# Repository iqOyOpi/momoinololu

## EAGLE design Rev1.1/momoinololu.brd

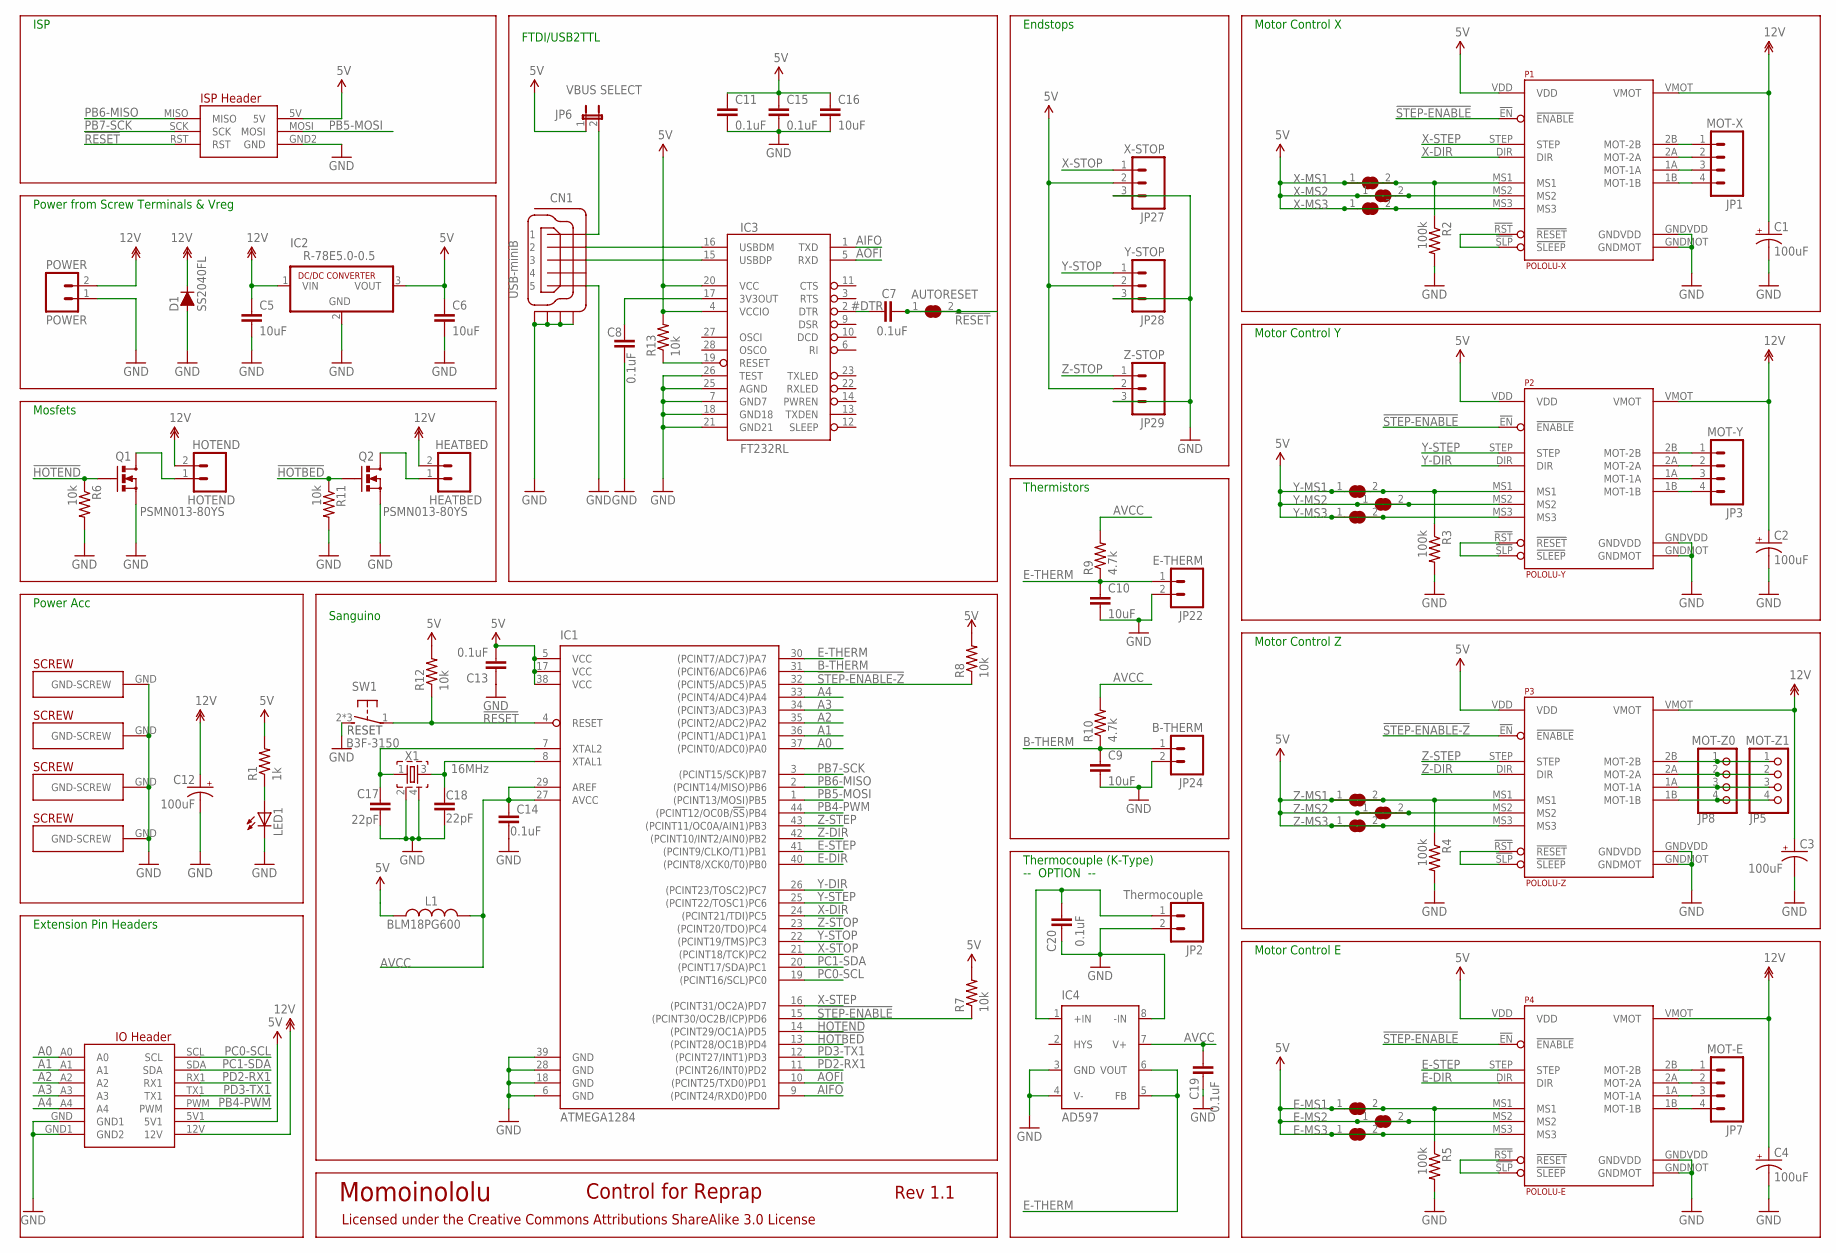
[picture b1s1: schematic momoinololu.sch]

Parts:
AUTORESET: SJ
C1, C2, C3, C4, C12: 100uF; UD-6,3X7,7_NICHICON
C5, C6, C9, C10, C16: 10uF; RCL_C1206K
C7, C8, C11, C13, C14, C15, C19, C20: 0.1uF; C0603
C17, C18: 22pF; C0603
CN1: USB-miniB; CON-HIROSE_UX60A-MB-5ST
D1: SS2040FL; SEMICON-SMD-IPC_SOD123
E-MS1, E-MS2, E-MS3: SJ
HEATBED: HEATBED; SCREWTERMINAL-5.08MM-2
HOTEND: HOTEND; SCREWTERMINAL-5.08MM-2
IC1: ATMEGA1284; TQFP44
IC2: R-78E5.0-0.5; SIP3
IC3: FT232RL; SSOP28DB
IC4: AD597; SO8
JP1: MOT-X; SPARKFUN_MOLEX-1X4
JP2: Thermocouple; SPARKFUN_1X02
JP3: MOT-Y; SPARKFUN_MOLEX-1X4
JP5: MOT-Z1; 1X04
JP6: VBUS SELECT; SPARKFUN_1X02
JP7: MOT-E; SPARKFUN_MOLEX-1X4
JP8: MOT-Z0; 1X04
JP22: E-THERM; SPARKFUN_1X02
JP24: B-THERM; SPARKFUN_1X02
JP27: X-STOP; SPARKFUN_MOLEX-1X3
JP28: Y-STOP; SPARKFUN_MOLEX-1X3
JP29: Z-STOP; SPARKFUN_MOLEX-1X3
L1: BLM18PG600; L0603
LED1: LEDSML0805; SML0805
P1: POLOLU-X; POLOLU-ALLEGRO_POLOLU-ALLEGRO-PTH
P2: POLOLU-Y; POLOLU-ALLEGRO_POLOLU-ALLEGRO-PTH
P3: POLOLU-Z; POLOLU-ALLEGRO_POLOLU-ALLEGRO-PTH
P4: POLOLU-E; POLOLU-ALLEGRO_POLOLU-ALLEGRO-PTH
POWER: POWER; SCREWTERMINAL-5.08MM-2
Q1, Q2: PSMN013-80YS; SOT669
R1: 1k; R0603
R2, R3, R4, R5: 100k; R0603
R6, R7, R8, R11, R12, R13: 10k; R0603
R9, R10: 4.7k; R0603
SW1: B3F-3150; B3F-31XX
U$17, U$20, U$25, U$31: PLATED-SCREW; PLATEDSCREW
U$24: SANGUINOLOLU_IO_HEADERSNOSCREW; SANGUINOLOLU_IO_HEADER_NOSCREW
X1: 16MHz; FA-238
X-MS1, X-MS2, X-MS3: SJ
Y-MS1, Y-MS2, Y-MS3: SJ
Z-MS1, Z-MS2, Z-MS3: SJ

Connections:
3V3: C8.1, IC3.17 (3V3OUT)
5V: C6.1, C11.1, C13.2, C15.1, C16.1, E-MS1.1, E-MS1.2, E-MS2.1, E-MS2.2, E-MS3.1, E-MS3.2, IC1.5 (VCC), IC1.17 (VCC), IC1.38 (VCC), IC2.3 (VOUT), IC3.4 (VCCIO), IC3.20 (VCC), JP6.1, JP27.2, JP28.2, JP29.2, L1.1, P1.MS1, P1.MS2, P1.MS3, P1.VDD, P2.MS1, P2.MS2, P2.MS3, P2.VDD, P3.MS1, P3.MS2, P3.MS3, P3.VDD, P4.MS1, P4.MS2, P4.MS3, P4.VDD, R1.2, R2.1, R3.1, R4.1, R5.1, R7.2, R8.2, R12.2, R13.2, U$24.5V, U$24.5V1, X-MS1.1, X-MS1.2, X-MS2.1, X-MS2.2, X-MS3.1, X-MS3.2, Y-MS1.1, Y-MS1.2, Y-MS2.1, Y-MS2.2, Y-MS3.1, Y-MS3.2, Z-MS1.1, Z-MS1.2, Z-MS2.1, Z-MS2.2, Z-MS3.1, Z-MS3.2
12V: C1.+, C2.+, C3.+, C4.+, C5.1, C12.+, D1.1 (C), HEATBED.2, HOTEND.2, IC2.1 (VIN), P1.VMOT, P2.VMOT, P3.VMOT, P4.VMOT, POWER.2, U$24.12V
!HOTBED: IC1.13 ((PCINT28/OC1B)PD4), Q2.4 (G), R11.1
!HOTEND: IC1.14 ((PCINT29/OC1A)PD5), Q1.4 (G), R6.1
!RESET: AUTORESET.1, AUTORESET.2, C7.1, IC1.4 (RESET), R12.1, SW1.1, U$24.RST
!STEP-ENABLE: IC1.15 ((PCINT30/OC2B/ICP)PD6), P1.!EN (!ENABLE), P2.!EN (!ENABLE), P4.!EN (!ENABLE), R7.1
!STEP-ENABLE-Z: IC1.32 ((PCINT5/ADC5)PA5), P3.!EN (!ENABLE), R8.1
#DTR: C7.2, IC3.2 (DTR)
+IN: C20.1, IC4.1 (+IN), JP2.1
A0: IC1.37 ((PCINT0/ADC0)PA0), U$24.A0
A1: IC1.36 ((PCINT1/ADC1)PA1), U$24.A1
A2: IC1.35 ((PCINT2/ADC2)PA2), U$24.A2
A3: IC1.34 ((PCINT3/ADC3)PA3), U$24.A3
A4: IC1.33 ((PCINT4/ADC4)PA4), U$24.A4
AIFO: IC1.9 ((PCINT24/RXD0)PD0), IC3.1 (TXD)
AOFI: IC1.10 ((PCINT25/TXD0)PD1), IC3.5 (RXD)
AVCC: C14.1, C19.1, IC1.27 (AVCC), IC1.29 (AREF), IC4.7 (V+), L1.2, R9.2, R10.2
B-THERM: C9.1, IC1.31 ((PCINT6/ADC6)PA6), JP24.1, R10.1
E-DIR: IC1.40 ((PCINT8/XCK0/T0)PB0), P4.DIR
E-MOT-1A: JP7.3, P4.1A (MOT-1A)
E-MOT-1B: JP7.4, P4.1B (MOT-1B)
E-MOT-2A: JP7.2, P4.2A (MOT-2A)
E-MOT-2B: JP7.1, P4.2B (MOT-2B)
E-RESETSLEEP: P4.!RST (!RESET), P4.!SLP (!SLEEP)
E-STEP: IC1.41 ((PCINT9/CLKO/T1)PB1), P4.STEP
E-THERM: C10.1, IC1.30 ((PCINT7/ADC7)PA7), IC4.5 (FB), IC4.6 (VOUT), JP22.1, R9.1
GND: C1.-, C2.-, C3.-, C4.-, C5.2, C6.2, C8.2, C9.2, C10.2, C11.2, C12.-, C13.1, C14.2, C15.2, C16.2, C17.2, C18.2, C19.2, C20.2, CN1.5, CN1.M1 (S1), CN1.M2 (S2), CN1.M3 (S3), CN1.M4 (S4), D1.2 (A), IC1.6 (GND), IC1.18 (GND), IC1.28 (GND), IC1.39 (GND), IC2.2 (GND), IC3.7 (GND7), IC3.18 (GND18), IC3.21 (GND21), IC3.25 (AGND), IC3.26 (TEST), IC4.3 (GND), IC4.4 (V-), IC4.8 (-IN), JP2.2, JP22.2, JP24.2, JP27.3, JP28.3, JP29.3, LED1.C, P1.GNDMOT, P1.GNDVDD, P2.GNDMOT, P2.GNDVDD, P3.GNDMOT, P3.GNDVDD, P4.GNDMOT, P4.GNDVDD, POWER.1, Q1.1 (S), Q1.2 (S), Q1.3 (S), Q2.1 (S), Q2.2 (S), Q2.3 (S), R2.2, R3.2, R4.2, R5.2, R6.2, R11.2, SW1.2 (S), SW1.3 (S), SW1.4 (S), U$17.GND, U$20.GND, U$24.GND (GND1), U$24.GND1 (GND2), U$24.GND2 (GND), U$25.GND, U$31.GND, X1.2, X1.4
HEATBED-GND: HEATBED.1, Q2.MB (D)
HOTEND-GND: HOTEND.1, Q1.MB (D)
LED1: LED1.A, R1.1
unnamed: C17.1, IC1.7 (XTAL2), X1.1
unnamed: IC3.19 (RESET), R13.1
unnamed: C18.1, IC1.8 (XTAL1), X1.3
unnamed: CN1.2, IC3.16 (USBDM)
unnamed: CN1.3, IC3.15 (USBDP)
PB4-PWM: IC1.44 ((PCINT12/OC0B/!SS!)PB4), U$24.PWM
PB5-MOSI: IC1.1 ((PCINT13/MOSI)PB5), U$24.MOSI
PB6-MISO: IC1.2 ((PCINT14/MISO)PB6), U$24.MISO
PB7-SCK: IC1.3 ((PCINT15/SCK)PB7), U$24.SCK
PC0-SCL: IC1.19 ((PCINT16/SCL)PC0), U$24.SCL
PC1-SDA: IC1.20 ((PCINT17/SDA)PC1), U$24.SDA
PD2-RX1: IC1.11 ((PCINT26/INT0)PD2), U$24.RX1
PD3-TX1: IC1.12 ((PCINT27/INT1)PD3), U$24.TX1
VBUS: CN1.1, JP6.2
X-DIR: IC1.24 ((PCINT21/TDI)PC5), P1.DIR
X-MOT-1A: JP1.3, P1.1A (MOT-1A)
X-MOT-1B: JP1.4, P1.1B (MOT-1B)
X-MOT-2A: JP1.2, P1.2A (MOT-2A)
X-MOT-2B: JP1.1, P1.2B (MOT-2B)
X-RESETSLEEP: P1.!RST (!RESET), P1.!SLP (!SLEEP)
X-STEP: IC1.16 ((PCINT31/OC2A)PD7), P1.STEP
X-STOP: IC1.21 ((PCINT18/TCK)PC2), JP27.1
Y-DIR: IC1.26 ((PCINT23/TOSC2)PC7), P2.DIR
Y-MOT-1A: JP3.3, P2.1A (MOT-1A)
Y-MOT-1B: JP3.4, P2.1B (MOT-1B)
Y-MOT-2A: JP3.2, P2.2A (MOT-2A)
Y-MOT-2B: JP3.1, P2.2B (MOT-2B)
Y-RESETSLEEP: P2.!RST (!RESET), P2.!SLP (!SLEEP)
Y-STEP: IC1.25 ((PCINT22/TOSC1)PC6), P2.STEP
Y-STOP: IC1.22 ((PCINT19/TMS)PC3), JP28.1
Z-DIR: IC1.42 ((PCINT10/INT2/AIN0)PB2), P3.DIR
Z-MOT-1A: JP5.3, JP8.3, P3.1A (MOT-1A)
Z-MOT-1B: JP5.4, JP8.4, P3.1B (MOT-1B)
Z-MOT-2A: JP5.2, JP8.2, P3.2A (MOT-2A)
Z-MOT-2B: JP5.1, JP8.1, P3.2B (MOT-2B)
Z-RESETSLEEP: P3.!RST (!RESET), P3.!SLP (!SLEEP)
Z-STEP: IC1.43 ((PCINT11/OC0A/AIN1)PB3), P3.STEP
Z-STOP: IC1.23 ((PCINT20/TDO)PC4), JP29.1

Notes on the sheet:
Motor Control X
Motor Control Y
Motor Control Z
Motor Control E
ISP
Thermistors
Endstops
Sanguino
FTDI/USB2TTL
Mosfets
Power Acc
Momoinololu
Rev 1.1
Control for Reprap
Licensed under the Creative Commons Attributions ShareAlike 3.0 License
Extension Pin Headers
Power from Screw Terminals & Vreg
Thermocouple (K-Type)
RESET
-- OPTION --

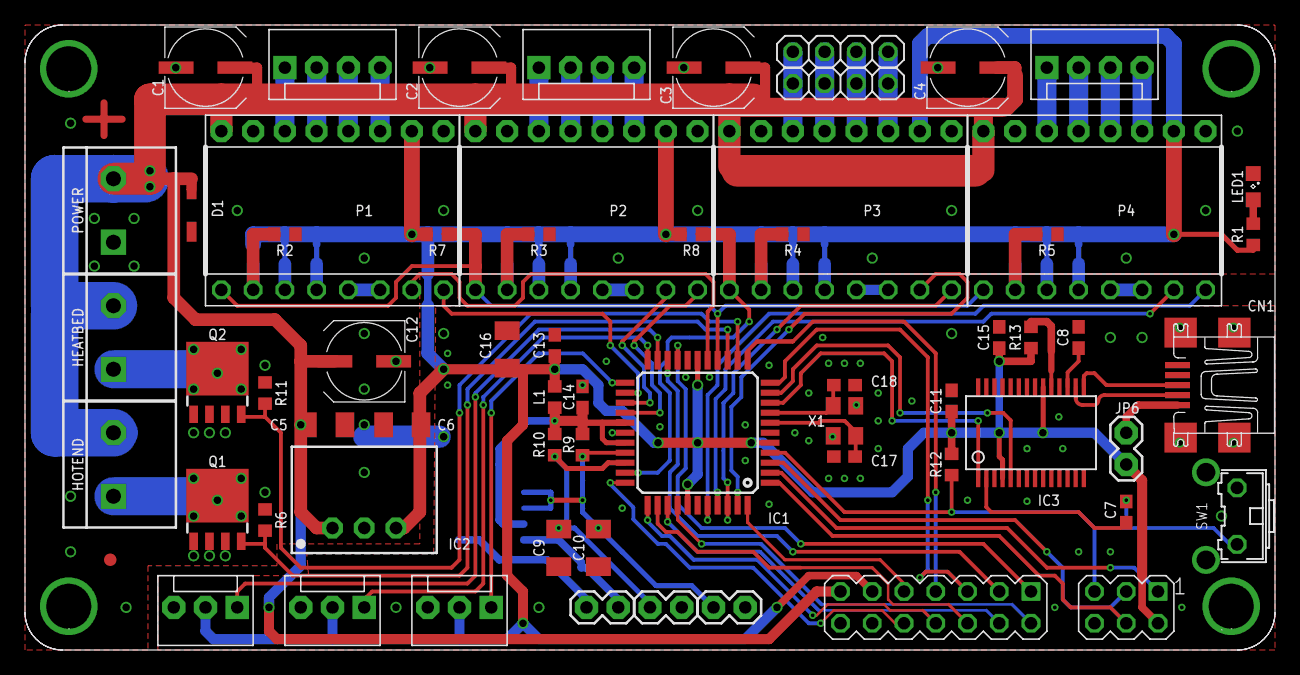
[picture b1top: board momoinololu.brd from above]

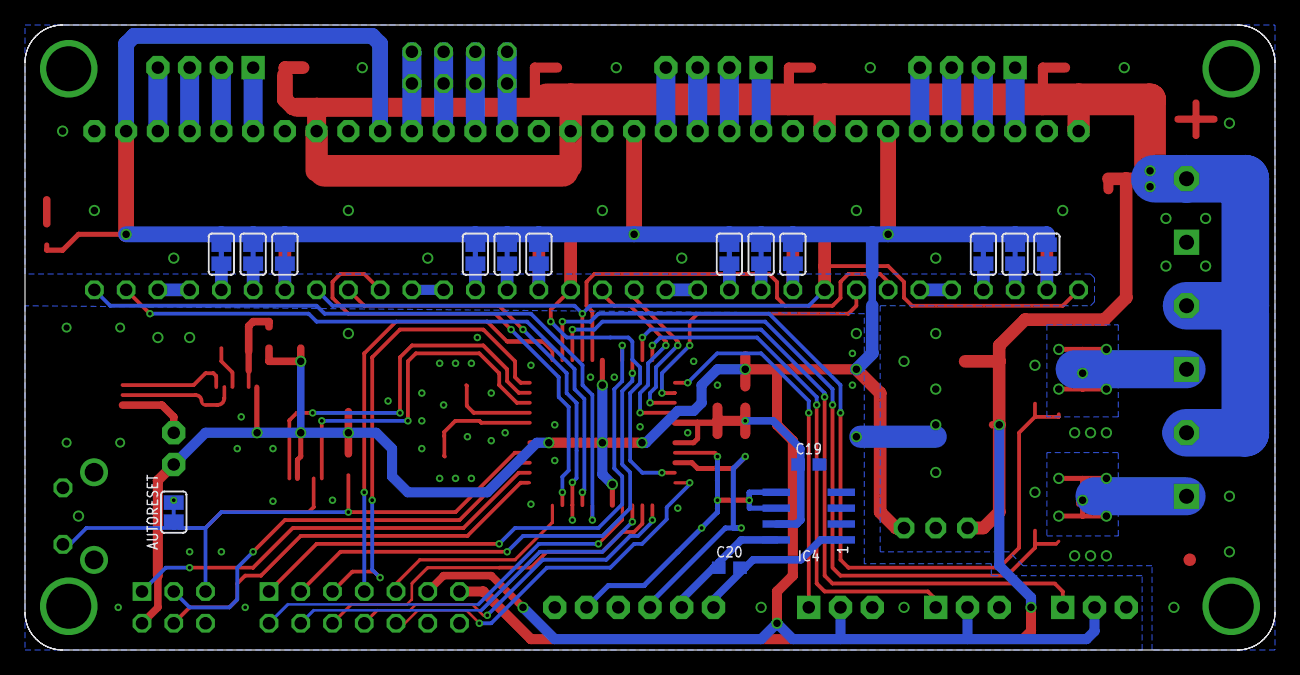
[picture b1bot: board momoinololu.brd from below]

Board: 2 copper layers, 100.0 x 50.0 mm, 82 parts (16 on the bottom side), 69 nets.

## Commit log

2014-08-01 :confetti_ball: Added .gitattributes & .gitignore files
2014-08-01 New Commit!
